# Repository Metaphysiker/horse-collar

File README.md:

# Horse Collar Monitoring System

Detects horse activity (standing, lying, rolling) and sends alerts for potential colic or distress. Device mounts on a chest belt.

---

## Current Status (2026-05-19)

Hardware ordered from BerryBase, delivery expected 2026-05-19 to 2026-05-21. Nothing built yet.

### Key constraints
- User has **no soldering tools** — all connections must be solderless
- User has a **personal server** for data logging
- Single stable box with some outside space

### Next steps
1. Receive hardware from BerryBase
2. Order weatherproof enclosure from reichelt.de or conrad.ch
3. Order UWB modules from AliExpress (`Makerfabs ESP32 UWB DW1000` x3)
4. Order mini breadboard (~170 pin) to hold boards together
5. Wire up BNO085 to HUZZAH32 via Qwiic cable
6. Set up Arduino IDE and flash firmware
7. Log baseline data for 1 week before building alerts
8. Set up Twilio voice call alerts

---

## Hardware

### Ordered from BerryBase

| Item | Product Nr | Price |
|---|---|---|
| Adafruit BNO085 IMU Breakout | ADA4754 | - |
| Adafruit HUZZAH32 ESP32 Feather (with stacking headers) | ADA3619 | CHF 21.95 |
| LiPo Battery 3.7V 2500mAh JST | LP-785060-J | - |
| 40pin Jumper Female-Female | - | - |
| Soldered easyC/Qwiic to Dupont Female cable | SOL-333314 | - |

### Still needed
- Weatherproof enclosure ~80x65x40mm (IP65/67) — order from reichelt.de or conrad.ch
- UWB modules for height detection (order from AliExpress): `Makerfabs ESP32 UWB DW1000` x3

---

## Wiring

### BNO085 → HUZZAH32
Via Qwiic/STEMMA QT to female jumper wire cable (SOL-333314):

| BNO085 | HUZZAH32 |
|---|---|
| VCC | 3V |
| GND | GND |
| SDA | SDA |
| SCL | SCL |

### Battery → HUZZAH32
JST connector plugs directly into HUZZAH32 JST socket. Charge via Micro-USB into HUZZAH32.

---

## Enclosure

- Target size: ~80x65x40mm
- Must be IP65/67 (weatherproof — horse sweats, rain)
- Fix components inside with double-sided velcro + polyethylene foam padding
- Use small cable tie on Qwiic cable to prevent connector strain
- Use mini breadboard (~170 pin) to hold HUZZAH32 and BNO085 together as one unit

---

## Detection Logic

### Sampling rate
- Read BNO085 every **1 second**
- Send data to server only on **state change** + heartbeat every **5 minutes**

### States
| State | Condition |
|---|---|
| Standing | Stable orientation, pitch/roll ~0° |
| Lying down | Pitch or roll > 60° for more than 10 seconds |
| Moving | Activity detected, upright orientation |
| Rolling (colic risk) | Activity detected + tilted orientation |

### BNO085 data to use
- **Gravity vector** — changes clearly when horse lies down
- **Absolute orientation / rotation vector** — pitch and roll angles
- **Activity classification** — stable, moving etc.
- **Linear acceleration** — sudden movements

### Battery monitoring
Read battery voltage via pin A13 on HUZZAH32:

| Voltage | Charge |
|---|---|
| 4.2V | 100% |
| 3.9V | ~60% |
| 3.7V | ~30% |
| 3.4V | ~5% |

---

## Data Logging (Server)

Log everything first to establish baseline — learn what normal looks like for this specific horse before building alerts.

### Payload (every state change)
```json
{
  "timestamp": "2026-05-19T08:00:00",
  "pitch": 12.3,
  "roll": 2.1,
  "activity": "stable",
  "acceleration": 0.12,
  "battery_voltage": 3.9,
  "battery_percent": 60,
  "state": "standing"
}
```

---

## Alerts (Twilio)

Voice call to mobile when abnormal state detected.

| Destination | Cost |
|---|---|
| Swiss mobile | ~$0.05 per call |
| Swiss landline | ~$0.01 per call |
| Twilio number | $1.15/month |

Trigger alert when:
- Horse rolling for more than 30 seconds (colic risk)
- Horse lying down for unusually long time
- Battery below 20%

---

## Future: UWB Height Detection

3x `Makerfabs ESP32 UWB DW1000` modules (~€60 total from AliExpress):
- Anchor 1: high (stable roof edge) — covers indoor + outdoor
- Anchor 2: low (stable wall, ground level)
- Tag: horse collar

Detects absolute height → confirms lying down independently of IMU orientation.
Combined with BNO085 gives much richer picture (lying + rolling = strong colic indicator).

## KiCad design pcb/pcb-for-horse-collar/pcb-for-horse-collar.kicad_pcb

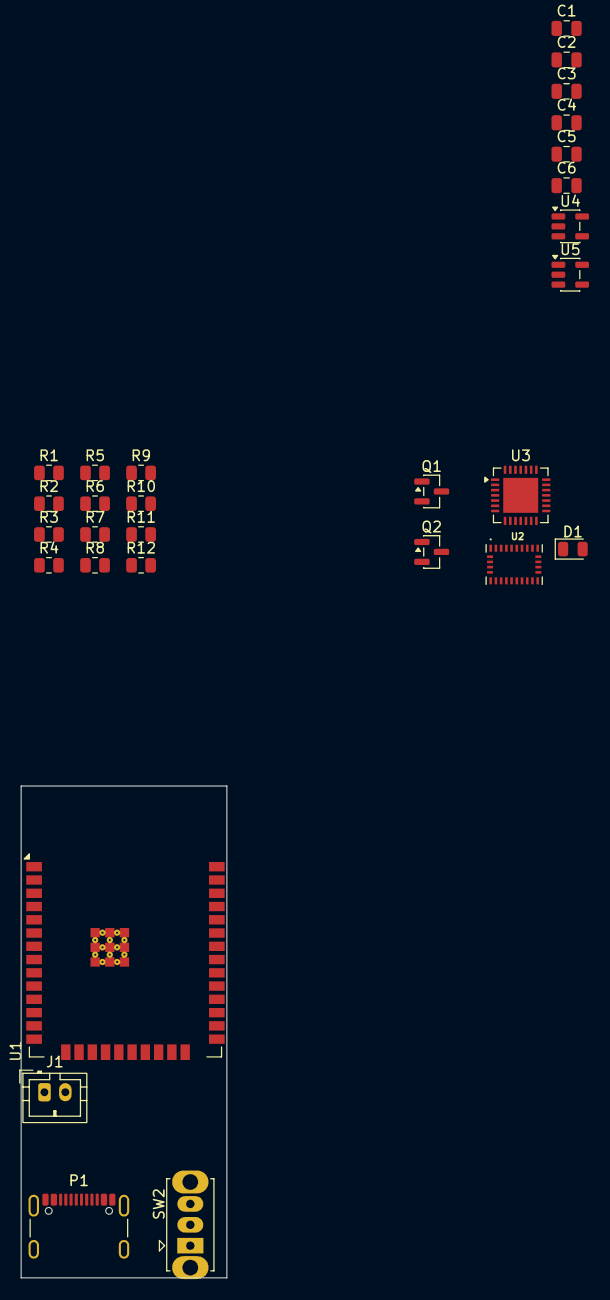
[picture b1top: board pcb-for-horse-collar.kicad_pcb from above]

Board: 2 copper layers, 19.7 x 47.1 mm, 29 parts (0 on the bottom side), 28 nets, no tracks yet.

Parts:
C1, C2, C3: 1µF; C_0805_2012Metric
C4, C6: 100nF; C_0805_2012Metric
C5: 4.7µF; C_0805_2012Metric
D1: LED; LED_0805_2012Metric
J1: Conn_01x02_Socket; JST_PH_B2B-PH-K_1x02_P2.00mm_Vertical
P1: USB_C_Receptacle_USB2.0_16P; USB_C_Receptacle_GCT_USB4105-xx-A_16P_TopMnt_Horizontal
Q1, Q2: S8050; SOT-23
R1: 2kΩ; R_0805_2012Metric
R2: 330Ω; R_0805_2012Metric
R3, R6, R7, R9: 10 kΩ; R_0805_2012Metric
R4, R8: 4.7 kΩ; R_0805_2012Metric
R5, R10: 5.1 kΩ; R_0805_2012Metric
R11, R12: 100 kΩ; R_0805_2012Metric
SW2: OS102011MS2Q; SW_Slide_SPDT_Straight_CK_OS102011MS2Q
U1: ESP32-WROOM-32E
U2: BNO085; IC_BNO085
U3: CP2102N-Axx-xQFN28; QFN-28-1EP_5x5mm_P0.5mm_EP3.35x3.35mm
U4: MCP73831-2-OT; SOT-23-5
U5: AP2112K-3.3; SOT-23-5

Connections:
/3V3: C2.1, R3.1, R4.1, R8.2, R9.2, U1.2 (VDD), U2.3 (VDD), U2.18 (~H_CS), U2.28 (VDDIO), U5.5 (VOUT)
/BNO_H_SCL: R4.2, U1.33 (IO21), U2.19 (H_SCL/SCK/RX)
/BNO_H_SDA: R8.1, U1.36 (IO22), U2.20 (H_SDA/H_MISO/TX)
/BNO_INT: U1.37 (IO23), U2.14 (~H_INT)
/BNO_RST: U1.10 (IO25), U2.11 (~RST)
/CP_DTR: Q2.1 (E), R6.1, U3.28 (~DTR)
/CP_RTS: Q1.1 (E), R7.1, U3.24 (~RTS)
/CP_RXD: U1.35 (TXD0/IO1), U3.25 (RXD)
/CP_TXD: U1.34 (RXD0/IO3), U3.26 (TXD)
/Q1_Collector: C4.2, Q1.3 (C), R3.2, U1.3 (EN)
/Q2_Collector: Q2.3 (C), U1.25 (IO0)
/USB_PLUG_D+: P1.A6 (D+), U3.4 (D+)
/USB_PLUG_D-: P1.A7 (D-), U3.5 (D-)
/VBAT+: C3.1, R11.1, SW2.1 (A), U5.1 (VIN), U5.3 (EN)
/VBAT_RAW: J1.2, SW2.2 (B), U4.3 (V_{BAT})
/VBUS: C1.1, D1.2 (A), P1.A4 (VBUS), P1.A9 (VBUS), P1.B4 (VBUS), P1.B9 (VBUS), U3.7 (VREGIN), U3.8 (VBUS), U4.4 (V_{DD})
GND: C1.2, C2.2, C3.2, C4.1, C5.1, C6.2, J1.1, P1.A1 (GND), P1.A12 (GND), P1.B1 (GND), P1.B12 (GND), R1.2, R5.2, R10.2, R12.1, U1.1 (GND), U1.15 (GND), U1.38 (GND), U1.39 (GND), U2.2 (GND), U2.5 (PS1), U2.6 (PS0/WAKE), U2.10 (CLKSEL0), U2.17 (SA0/H_MOSI), U2.25 (GNDIO), U3.3 (GND), U3.29 (GND), U4.2 (V_{SS}), U5.2 (GND)
unnamed: D1.1 (K), R2.2
unnamed: P1.A5 (CC1), R5.1
unnamed: P1.B5 (CC2), R10.1
unnamed: Q1.2 (B), R6.2
unnamed: Q2.2 (B), R7.2
unnamed: R11.2, R12.2, U1.4 (SENSOR_VP)
unnamed: C6.1, U2.9 (CAP)
unnamed: R9.1, U2.4 (~BOOT)
unnamed: C5.2, U3.6 (VDD)
unnamed: R1.1, U4.5 (PROG)
unnamed: R2.1, U4.1 (STAT)

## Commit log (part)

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2026-05-19 Add webapi, svelte and huzzah.
2026-05-19 Add deploy-scripts.
2026-05-19 Add nav, calibrate-page, SensorReading data.
2026-05-20 Add config and turn off wifi periodically.
2026-05-22 Add configs, flash and monitor.
2026-05-23 Update to read battery more accurately.
2026-05-23 Update Guardian to go away from calibrating and detect from context.
2026-05-23 Update Guardian to use CollarConfig.
2026-05-23 Trigger alarm on ackend.
2026-05-25 Add analysis page.
2026-05-25 Update time select in HorseAnalysis Page.
2026-05-25 Add percentiles to Analysis.
2026-05-25 Visualize percentiles.
2026-05-25 Add outlier analysis.
2026-05-25 Update orientation demo.
2026-05-25 Show outlier count.
2026-05-25 Add dense cluster.
2026-05-25 Update extreme analysis slider.
2026-05-25 Go till 9 for sigma range.
2026-05-25 Bump standard deviation to 12
2026-05-25 Fix potential leak in guardian
2026-05-25 Add limit for SensorReadings.
2026-05-25 Fix limit issue.
2026-05-25 Add alarm regarding tilt and horse roll.
2026-05-25 Add message to know which strategy is being used.
2026-05-25 Rename unknown in ReadingsController.
2026-05-25 Fix switch in ReadingController.
2026-05-25 Change baseline for horse roll.
2026-05-26 Add horse roll analysis.
2026-05-26 Activity timeline.
2026-05-26 German translation in HorseDetailPage.
2026-05-26 Send alarm when 3 consecutive readings are sent.
2026-05-27 Add casing information and stls.
2026-05-27 Add lipo-battery.scad.
2026-05-27 Add stl files.
2026-05-27 Update holes to match bno
2026-05-27 Add reference so electronics does not get printed.
2026-05-27 Add stl file for print.
2026-05-28 Add scad with heat inserts.
2026-05-28 Hide ox_body.
2026-05-29 Draw body.
2026-05-29 Add battery_clearance.
2026-05-29 Move pillars into the edge.
2026-05-29 Move positions of component for better wiring.
2026-05-29 Prepare print-build.
2026-05-29 Add lid assembled boolean.
2026-06-02 Add BnoConnected and sleep before critical battery.
2026-06-02 Add quaternion to Sensorreading.
2026-06-02 Fix quaternion-values.
2026-06-02 Head inserts changes.
2026-06-02 Update battery buffer.
2026-06-02 Add quaternion to table.
2026-06-02 Add state for config in HorseDetailPage.
2026-06-03 Add horse animation for checking orientation.
2026-06-03 Add calibration step and clear after set.
2026-06-05 Add int-test.ino to test int-wire.
2026-06-05 Update int-test.ino.
2026-06-06 Add custom ino.
2026-06-06 Add heartbeat and use quaternion to detect sidewards.
2026-06-06 Add debug for sensor interval
2026-06-09 Add SensorReadingV2.
2026-06-09 Update custom.ino to send SensorReadingsV2.
2026-06-09 Add timestamp for readings and send to backend.
2026-06-09 WIP: Calibrate never happens.
2026-06-10 Update custome to use wdt timeout, no millies and print reason.
2026-06-12 Add detectPostureV2 too.
2026-06-13 Update detectPostureV2
2026-06-13 Add simple version.
2026-06-18 Add huzzah-main.
2026-06-18 Update Main and related items.
2026-06-19 Update HorseConfigPage and main.
2026-06-19 Update main to use v3 detection to select mode.
2026-06-19 Add PowerMode and MaintenanceWakeIntervalUs.
2026-06-19 Use global secureClient, use reuse, clear after recalibrate
2026-06-19 Update main to clear recalibrate.
2026-06-19 Apply fixes from gemini.
2026-06-19 Remove wire end and wire begin.
2026-06-20 Remove sendEveryN.
2026-06-20 Show readings for V2 data.
2026-06-20 Trying to make horse appear correctly.
2026-06-21 Tell heartbeatinterval to use BsonType.String.
2026-06-23 Add sendEveryN again because flashed software is older.
2026-06-23 Go into maintenance mode when battery goes low and remove reboot when sendReading fails.
2026-06-23 Add ntfy notification when reboot and recalibrate clears.
2026-06-23 Add CronjobController.cs
2026-06-23 Add detectPostureV4 to main.
2026-06-24 Comment out WiFi.setxPower to 8.5 dbm.
2026-06-27 Update main to check battery in loop.
2026-06-27 Add debug for logger.
2026-06-27 Update main to skip transmission if there is no internet and comment out ntfy for get config and create status.
2026-06-27 Failed ino to flash.
2026-06-27 Deep sleep after bno not found.
2026-06-27 Add more RTC_DATA_ATTR and add lastTimeSyncUs.
2026-06-29 Don't send ntfy if device is in maintenance mode.
